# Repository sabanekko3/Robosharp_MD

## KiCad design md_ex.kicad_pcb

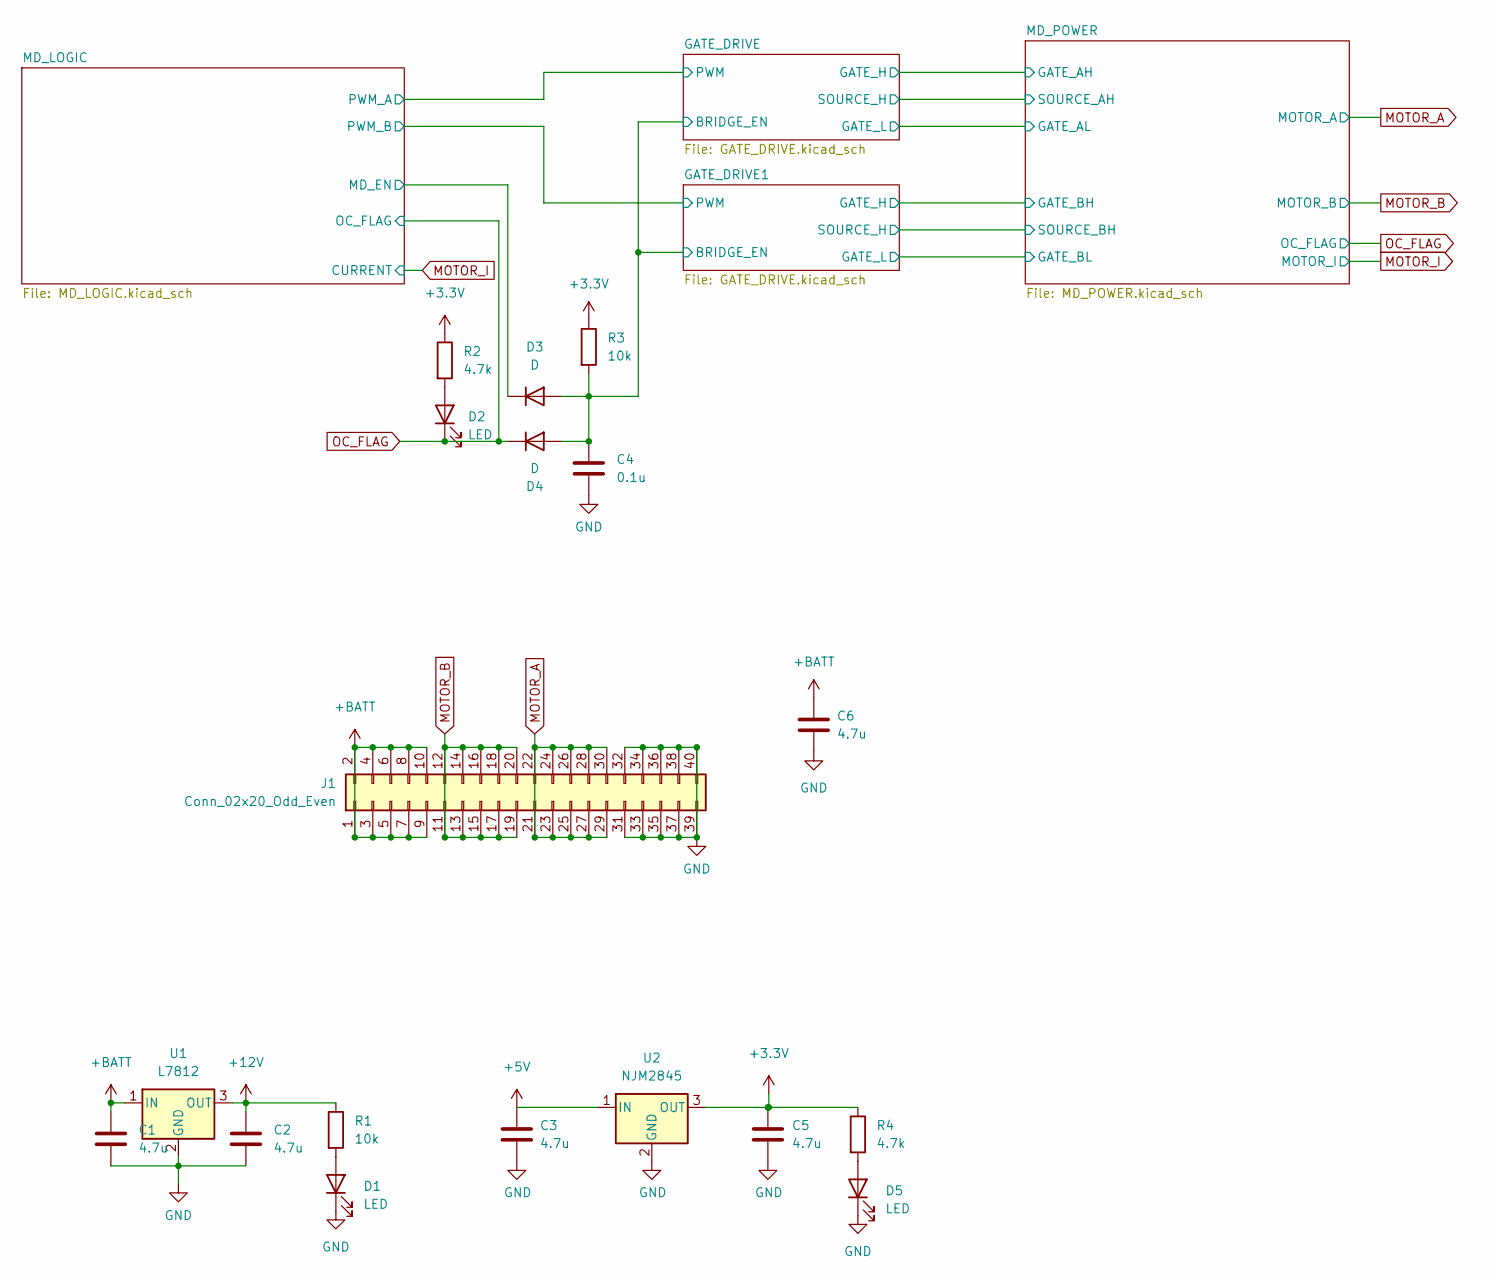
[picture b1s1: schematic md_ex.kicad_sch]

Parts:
C1, C2, C3, C5, C6: 4.7u; C_0805_2012Metric_Pad1.18x1.45mm_HandSolder
C4: 0.1u; C_0603_1608Metric_Pad1.08x0.95mm_HandSolder
D1, D2, D5: LED; LED_0603_1608Metric_Pad1.05x0.95mm_HandSolder
D3, D4: D; D_SOD-123F
J1: Conn_02x20_Odd_Even; PinHeader_2x20_P2.54mm_Horizontal
R1, R3: 10k; R_0603_1608Metric_Pad0.98x0.95mm_HandSolder
R2, R4: 4.7k; R_0603_1608Metric_Pad0.98x0.95mm_HandSolder
U1: L7812; TO-252-2
U2: NJM2845; TO-252-2

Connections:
+3V3: C5.1, R2.1, R3.1, R4.1, U2.3 (OUT); also elsewhere on the board
+5V: C3.1, U2.1 (IN); also elsewhere on the board
+12V: C2.1, R1.1, U1.3 (OUT); also elsewhere on the board
+BATT: C1.1, C6.1, J1.1, J1.2, J1.3, J1.4, J1.5, J1.6, J1.7, J1.8, J1.9, J1.10, U1.1 (IN); also elsewhere on the board
/GATE_DRIVE/BRIDGE_EN: C4.1, D3.2 (A), D4.2 (A), R3.2; also elsewhere on the board
/MD_LOGIC/MD_EN: D3.1 (K); also elsewhere on the board
GND: C1.2, C2.2, C3.2, C4.2, C5.2, C6.2, D1.1 (K), D5.1 (K), J1.31, J1.32, J1.33, J1.34, J1.35, J1.36, J1.37, J1.38, J1.39, J1.40, U1.2 (GND), U2.2 (GND); also elsewhere on the board
MOTOR_A: J1.21, J1.22, J1.23, J1.24, J1.25, J1.26, J1.27, J1.28, J1.29, J1.30; also elsewhere on the board
MOTOR_B: J1.11, J1.12, J1.13, J1.14, J1.15, J1.16, J1.17, J1.18, J1.19, J1.20; also elsewhere on the board
unnamed: D1.2 (A), R1.2
unnamed: D2.2 (A), R2.2
unnamed: D5.2 (A), R4.2
OC_FLAG: D2.1 (K), D4.1 (K); also elsewhere on the board

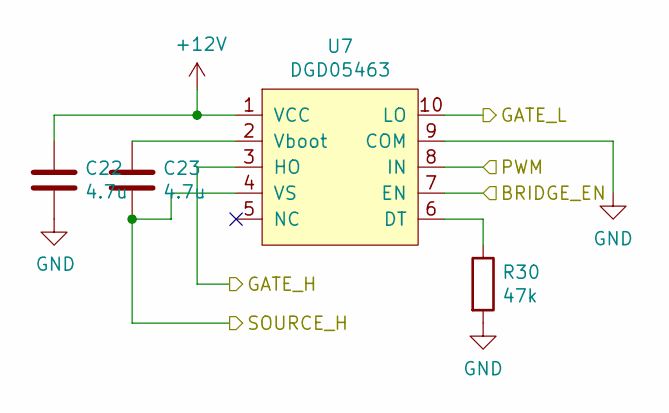
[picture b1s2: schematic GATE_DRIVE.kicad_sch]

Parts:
C22, C23: 4.7u; C_0805_2012Metric_Pad1.18x1.45mm_HandSolder
R30: 47k; R_0603_1608Metric_Pad0.98x0.95mm_HandSolder
U7: DGD05463; DFN-10-1EP_3x3mm_P0.5mm_EP1.55x2.48mm

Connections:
+12V: C22.1, U7.1 (VCC); also elsewhere on the board
/GATE_DRIVE1/GATE_H: U7.3 (HO); also elsewhere on the board
/GATE_DRIVE1/GATE_L: U7.10 (LO); also elsewhere on the board
/GATE_DRIVE1/PWM: U7.8 (IN); also elsewhere on the board
/GATE_DRIVE1/SOURCE_H: C23.2, U7.4 (VS); also elsewhere on the board
/GATE_DRIVE/BRIDGE_EN: U7.7 (EN); also elsewhere on the board
GND: C22.2, R30.2, U7.9 (COM); also elsewhere on the board
unnamed: C23.1, U7.2 (Vboot)
unnamed: R30.1, U7.6 (DT)

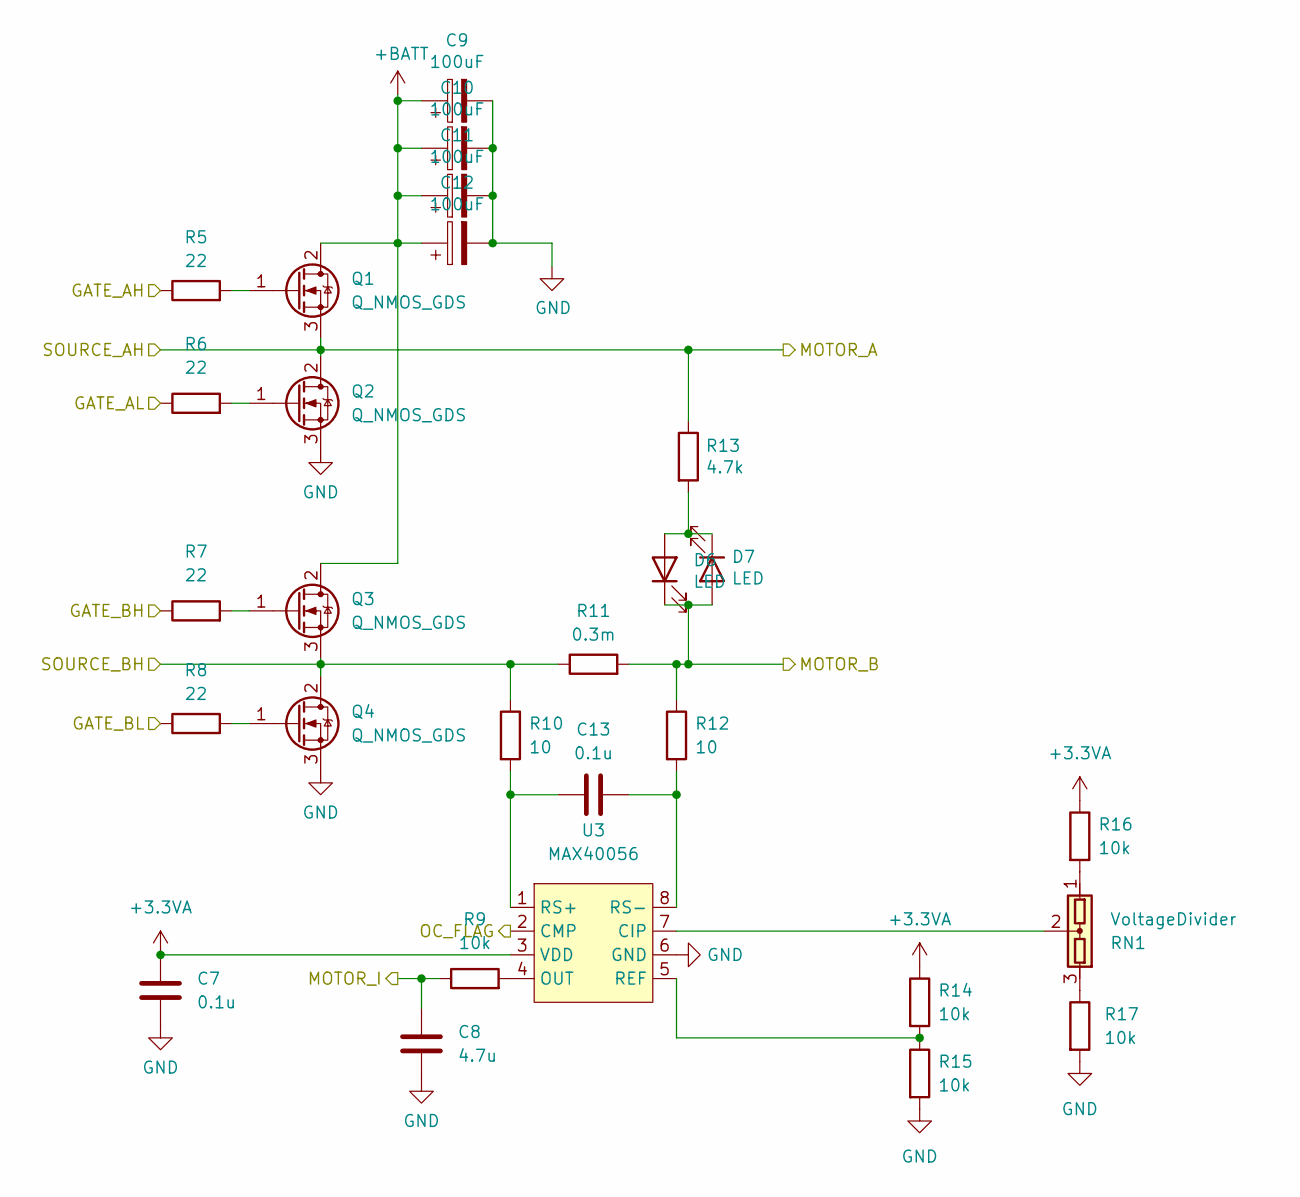
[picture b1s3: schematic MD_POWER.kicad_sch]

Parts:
C7, C13: 0.1u; C_0603_1608Metric_Pad1.08x0.95mm_HandSolder
C8: 4.7u; C_0805_2012Metric_Pad1.18x1.45mm_HandSolder
C9, C10, C11, C12: 100uF; CP_Elec_10x10
D6, D7: LED; LED_0603_1608Metric_Pad1.05x0.95mm_HandSolder
Q1, Q2, Q3, Q4: Q_NMOS_GDS; TO-263-2
R5, R6, R7, R8: 22; R_0603_1608Metric_Pad0.98x0.95mm_HandSolder
R9, R14, R15, R16, R17: 10k; R_0603_1608Metric_Pad0.98x0.95mm_HandSolder
R10, R12: 10; R_0603_1608Metric_Pad0.98x0.95mm_HandSolder
R11: 0.3m; PU2512
R13: 4.7k; R_0603_1608Metric_Pad0.98x0.95mm_HandSolder
RN1: VoltageDivider; Potentiometer_Bourns_3224J_Horizontal
U3: MAX40056; MSOP-8_3x3mm_P0.65mm

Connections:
+3.3VA: C7.1, R14.1, R16.1, U3.3 (VDD); also elsewhere on the board
+BATT: C9.1, C10.1, C11.1, C12.1, Q1.2 (D), Q3.2 (D); also elsewhere on the board
/GATE_DRIVE1/GATE_H: R7.1; also elsewhere on the board
/GATE_DRIVE1/GATE_L: R8.1; also elsewhere on the board
/GATE_DRIVE1/SOURCE_H: Q3.3 (S), Q4.2 (D), R10.1, R11.1; also elsewhere on the board
/GATE_DRIVE/GATE_H: R5.1; also elsewhere on the board
/GATE_DRIVE/GATE_L: R6.1; also elsewhere on the board
GND: C7.2, C8.2, C9.2, C10.2, C11.2, C12.2, Q2.3 (S), Q4.3 (S), R15.2, R17.2, U3.6 (GND); also elsewhere on the board
MOTOR_A: Q1.3 (S), Q2.2 (D), R13.1; also elsewhere on the board
MOTOR_B: D6.1 (K), D7.2 (A), R11.2, R12.1; also elsewhere on the board
MOTOR_I: C8.1, R9.1; also elsewhere on the board
unnamed: C13.1, R10.2, U3.1 (RS+)
unnamed: C13.2, R12.2, U3.8 (RS-)
unnamed: D6.2 (A), D7.1 (K), R13.2
unnamed: Q1.1 (G), R5.2
unnamed: Q2.1 (G), R6.2
unnamed: Q3.1 (G), R7.2
unnamed: Q4.1 (G), R8.2
unnamed: R9.2, U3.4 (OUT)
unnamed: R14.2, R15.1, U3.5 (REF)
unnamed: R16.2, RN1.1
unnamed: R17.1, RN1.3
unnamed: RN1.2, U3.7 (CIP)
OC_FLAG: U3.2 (CMP); also elsewhere on the board

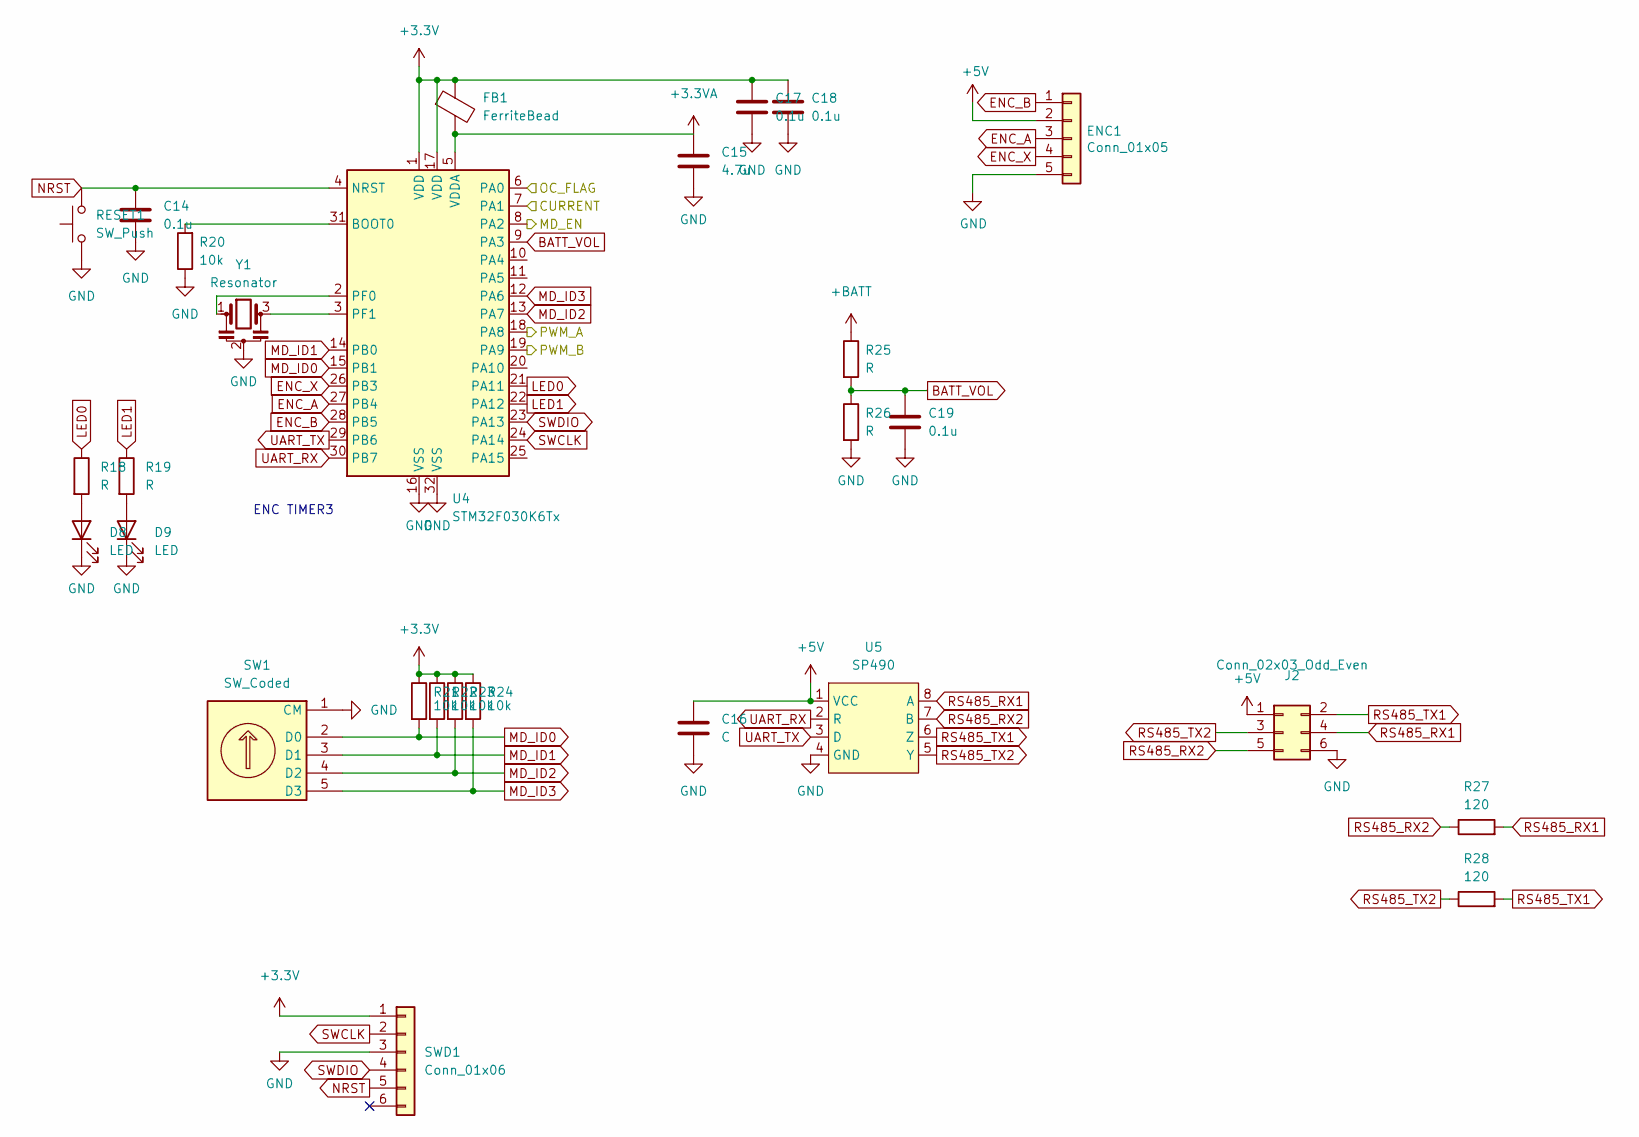
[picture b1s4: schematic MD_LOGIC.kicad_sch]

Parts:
C14, C17, C18, C19: 0.1u; C_0603_1608Metric_Pad1.08x0.95mm_HandSolder
C15: 4.7u; C_0805_2012Metric_Pad1.18x1.45mm_HandSolder
C16: C; C_0603_1608Metric_Pad1.08x0.95mm_HandSolder
D8, D9: LED; LED_0603_1608Metric_Pad1.05x0.95mm_HandSolder
ENC1: Conn_01x05; XA_05_Horizontal
FB1: FerriteBead; L_0603_1608Metric_Pad1.05x0.95mm_HandSolder
J2: Conn_02x03_Odd_Even; IDC-Header_2x03_P2.54mm_Horizontal
R18, R19, R25, R26: R; R_0603_1608Metric_Pad0.98x0.95mm_HandSolder
R20, R21, R22, R23, R24: 10k; R_0603_1608Metric_Pad0.98x0.95mm_HandSolder
R27, R28: 120; R_0603_1608Metric_Pad0.98x0.95mm_HandSolder
RESET1: SW_Push; KMR621NG
SW1: SW_Coded; ROTARY_DIP
SWD1: Conn_01x06; PinHeader_1x06_P2.54mm_Vertical
U4: STM32F030K6Tx; LQFP-32_7x7mm_P0.8mm
U5: SP490; SOIC-8_3.9x4.9mm_P1.27mm
Y1: Resonator; Resonator_SMD_Murata_CSTxExxV-3Pin_3.0x1.1mm_HandSoldering

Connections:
+3.3VA: C15.1, FB1.2, U4.5 (VDDA); also elsewhere on the board
+3V3: C17.1, C18.1, FB1.1, R21.1, R22.1, R23.1, R24.1, SWD1.1, U4.1 (VDD), U4.17 (VDD); also elsewhere on the board
+5V: C16.1, ENC1.2, J2.1, U5.1 (VCC); also elsewhere on the board
+BATT: R25.1; also elsewhere on the board
/GATE_DRIVE1/PWM: U4.19 (PA9); also elsewhere on the board
/GATE_DRIVE/PWM: U4.18 (PA8); also elsewhere on the board
/MD_LOGIC/MD_EN: U4.8 (PA2); also elsewhere on the board
BATT_VOL: C19.1, R25.2, R26.1, U4.9 (PA3)
ENC_A: ENC1.3, U4.27 (PB4)
ENC_B: ENC1.1, U4.28 (PB5)
ENC_X: ENC1.4, U4.26 (PB3)
GND: C14.2, C15.2, C16.2, C17.2, C18.2, C19.2, D8.1 (K), D9.1 (K), ENC1.5, J2.6, R20.1, R26.2, RESET1.1, SW1.1 (CM), SWD1.3, U4.16 (VSS), U4.32 (VSS), U5.4 (GND), Y1.2; also elsewhere on the board
LED0: R18.1, U4.21 (PA11)
LED1: R19.1, U4.22 (PA12)
MD_ID0: R21.2, SW1.2 (D0), U4.15 (PB1)
MD_ID1: R22.2, SW1.3 (D1), U4.14 (PB0)
MD_ID2: R23.2, SW1.4 (D2), U4.13 (PA7)
MD_ID3: R24.2, SW1.5 (D3), U4.12 (PA6)
MOTOR_I: U4.7 (PA1); also elsewhere on the board
NRST: C14.1, RESET1.2, SWD1.5, U4.4 (NRST)
unnamed: D8.2 (A), R18.2
unnamed: D9.2 (A), R19.2
unnamed: R20.2, U4.31 (BOOT0)
unnamed: U4.2 (PF0), Y1.1
unnamed: U4.3 (PF1), Y1.3
OC_FLAG: U4.6 (PA0); also elsewhere on the board
RS485_RX1: J2.4, R27.2, U5.8 (A)
RS485_RX2: J2.5, R27.1, U5.7 (B)
RS485_TX1: J2.2, R28.2, U5.6 (Z)
RS485_TX2: J2.3, R28.1, U5.5 (Y)
SWCLK: SWD1.2, U4.24 (PA14)
SWDIO: SWD1.4, U4.23 (PA13)
UART_RX: U4.30 (PB7), U5.2 (R)
UART_TX: U4.29 (PB6), U5.3 (D)

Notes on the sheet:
ENC TIMER3

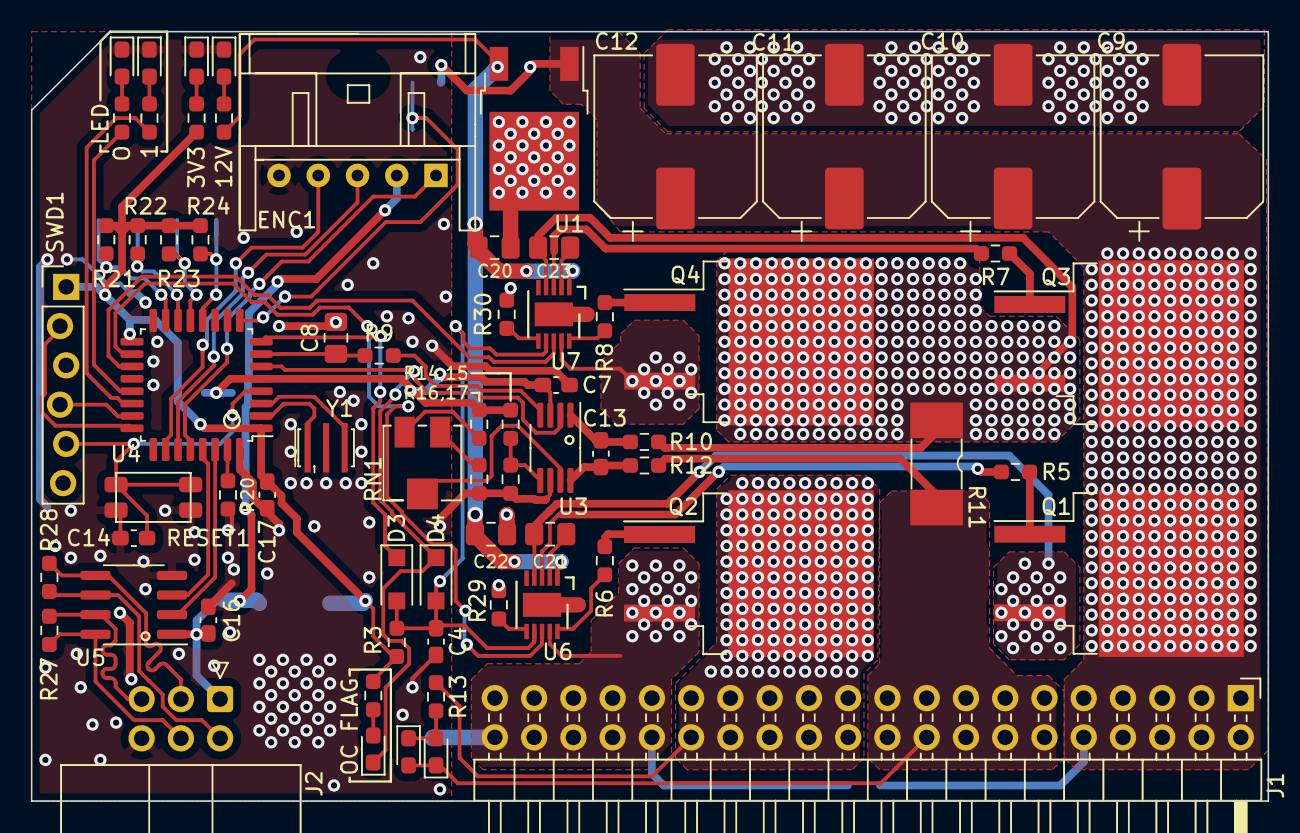
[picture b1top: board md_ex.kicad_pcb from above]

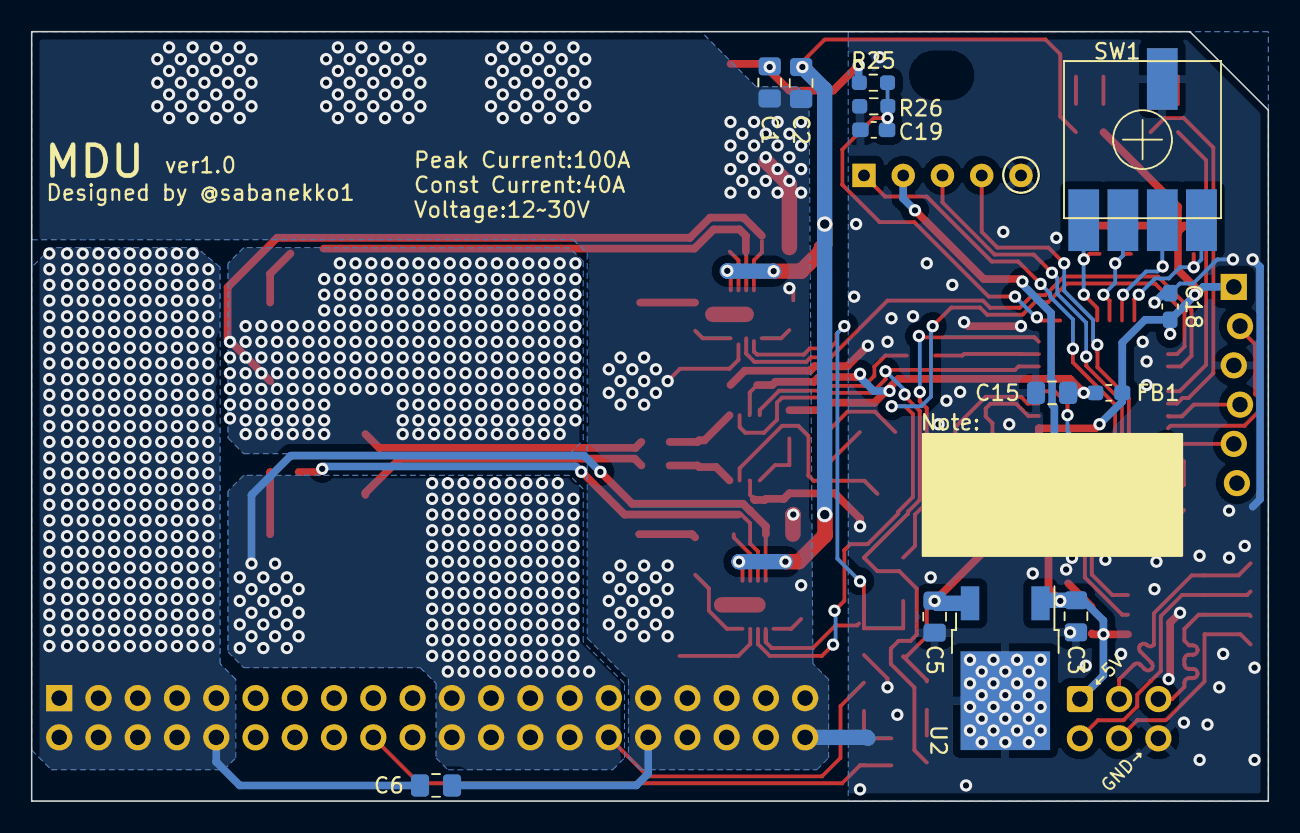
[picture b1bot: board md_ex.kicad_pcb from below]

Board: 2 copper layers, 80.0 x 49.8 mm, 82 parts (13 on the bottom side), 62 nets.

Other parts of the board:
C20, C21: 4.7u; C_0805_2012Metric_Pad1.18x1.45mm_HandSolder
R29: 47k; R_0603_1608Metric_Pad0.98x0.95mm_HandSolder
U6: DGD05463; DFN-10-1EP_3x3mm_P0.5mm_EP1.55x2.48mm

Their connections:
+12V: C20.1, U6.1 (VCC); also elsewhere on the board
/GATE_DRIVE/BRIDGE_EN: U6.7 (EN); also elsewhere on the board
/GATE_DRIVE/GATE_H: U6.3 (HO); also elsewhere on the board
/GATE_DRIVE/GATE_L: U6.10 (LO); also elsewhere on the board
/GATE_DRIVE/PWM: U6.8 (IN); also elsewhere on the board
GND: C20.2, R29.2, U6.9 (COM); also elsewhere on the board
MOTOR_A: C21.2, U6.4 (VS); also elsewhere on the board
unnamed: C21.1, U6.2 (Vboot)
unnamed: R29.1, U6.6 (DT)

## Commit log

2023-06-08 first
